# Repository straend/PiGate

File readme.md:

## Simple installation and compilation of MySensors gateway
Modify MQTT_HOST in `install.sh`
 
And run ```bash install.sh```

### SensorBender PiGate Pins
| rPI | BCM | PiGate |
| :----: | :---: | :----|
| **nRF24** |
|  15  |  24  |  nRF24 IRQ  |
|  22  |  25  |  nRF24 CE |
|  24  |  8  |  nRF24 CS |
| **RFM95** |
|  13  |  23  |  RFM95 IRQ (DIO0) |
|  26  |  7  |  RFM95 CS  |
| **Common** |
|  19  |  10  |  MOSI  |
|  21  |  9  |  MISO  |
|  23  |  11  |  SCK   |

# Schema

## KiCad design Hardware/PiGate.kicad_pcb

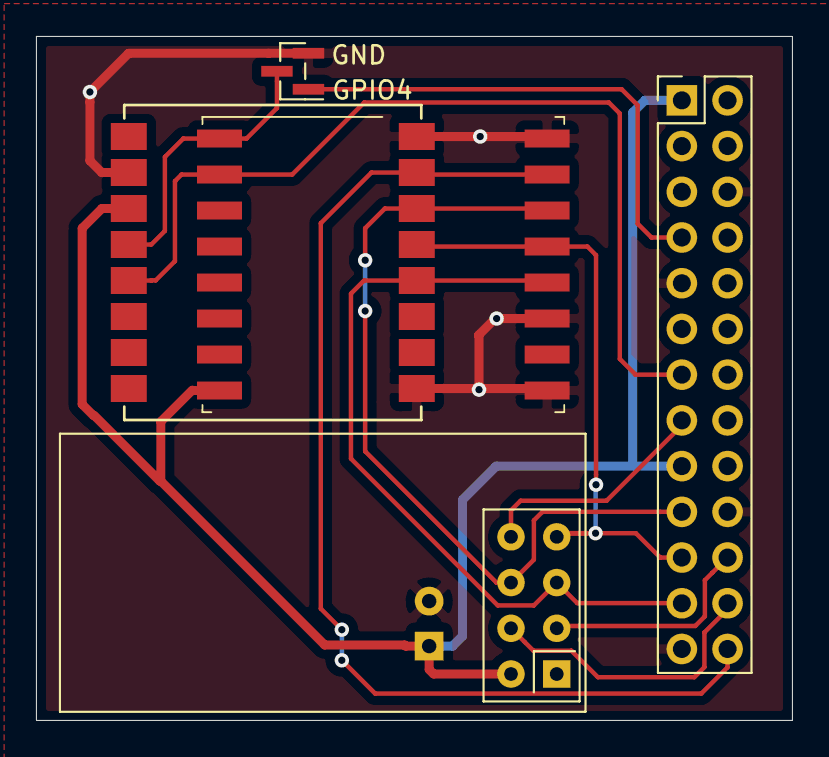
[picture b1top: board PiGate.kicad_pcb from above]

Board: 2 copper layers, 42.0 x 38.0 mm, 6 parts (1 on the bottom side), 12 nets.

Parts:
C2: CP; CP_Radial_D8.0mm_P2.50mm
J1: Conn_02x13_Odd_Even; PinHeader_2x13_P2.54mm_Vertical
J2: Conn_01x03_Male; PinHeader_1x03_P1.00mm_Vertical_SMD_Pin1Left
U1: NRF24L01_Breakout; nRF24L01_Breakout
U2: RFM69W; HOPERF_RFM69HW
U3: Ai-Thinker-Ra-01; Ai-Thinker-Ra-01-LoRa

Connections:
+3V3: C2.1, J1.1, J1.17, U1.2, U2.8, U3.3
GND: C2.2, J1.6, J1.9, J1.20, J1.25, J2.3, U1.1, U2.9, U2.11, U2.16, U3.2, U3.9, U3.16
MISO: J1.21, U1.7, U2.13, U3.13
MOSI: J1.19, U1.6, U2.14, U3.14
unnamed: J1.7, J2.1
unnamed: J2.2, U2.1, U3.4
RFM_IRQ: J1.13, U2.2, U3.5
RFM_NSS: J1.26, U2.15, U3.15
SCK: J1.23, U1.5, U2.12, U3.12
nRF_CE: J1.22, U1.3
nRF_CSN: J1.24, U1.4
nRF_IRQ: J1.15, U1.8

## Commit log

2021-01-04 First
2021-01-04 Add schematic image
